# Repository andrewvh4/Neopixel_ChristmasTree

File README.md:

# Neopixel_ChristmasTree
A small, festive desk ornament

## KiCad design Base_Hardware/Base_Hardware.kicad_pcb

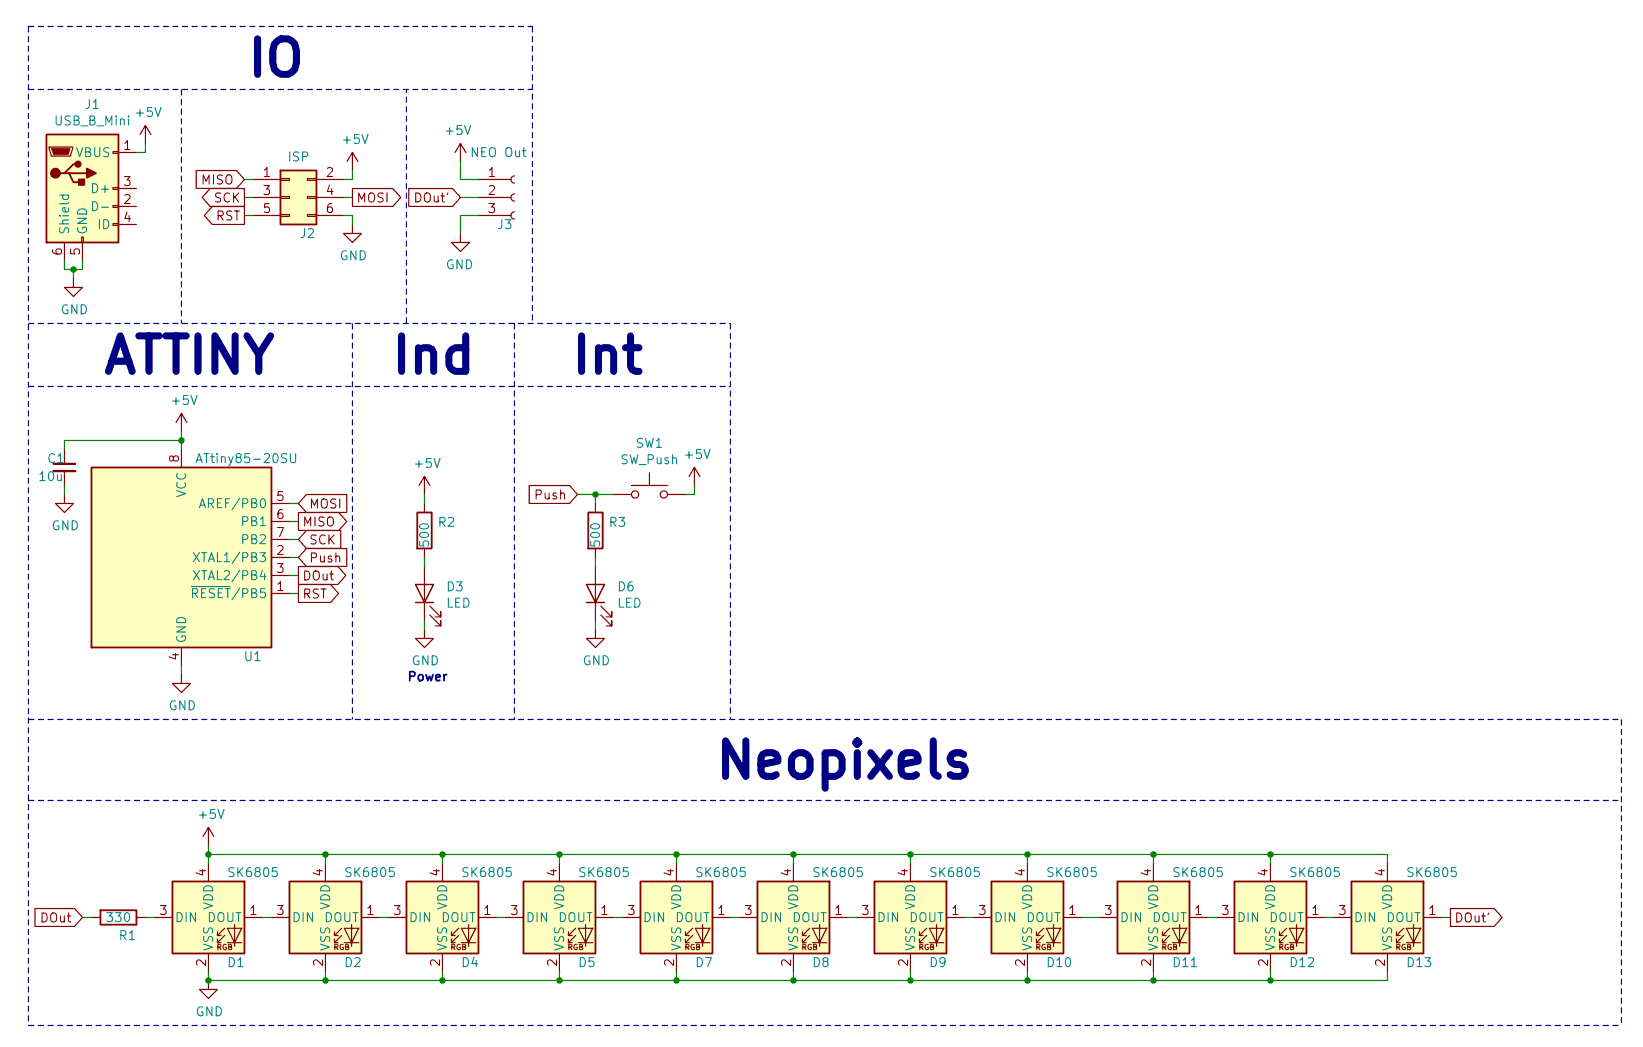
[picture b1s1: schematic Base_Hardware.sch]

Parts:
C1: 10u; C_0603_1608Metric_Pad1.05x0.95mm_HandSolder
D1, D2, D4, D5, D7, D8, D9, D10, D11, D12, D13: SK6805; SK6805-EC
D3, D6: LED; LED_0603_1608Metric_Pad1.05x0.95mm_HandSolder
J1: USB_B_Mini; MiniUSB_SMD
J2: ISP; IDC-Header_2x03_P2.54mm_Vertical
J3: NEO Out; PinSocket_1x03_P2.54mm_Vertical
R1: 330; R_0603_1608Metric_Pad1.05x0.95mm_HandSolder
R2, R3: 500; R_0603_1608Metric_Pad1.05x0.95mm_HandSolder
SW1: SW_Push; SW_SPST_PTS645
U1: ATtiny85-20SU; SOIJ-8_5.3x5.3mm_P1.27mm

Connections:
+5V: C1.1, D1.4 (VDD), D2.4 (VDD), D4.4 (VDD), D5.4 (VDD), D7.4 (VDD), D8.4 (VDD), D9.4 (VDD), D10.4 (VDD), D11.4 (VDD), D12.4 (VDD), D13.4 (VDD), J1.1 (VBUS), J2.2, J3.1, R2.1, SW1.2, U1.8 (VCC)
DOut: R1.2, U1.3 (XTAL2/PB4)
DOut': D13.1 (DOUT), J3.2
GND: C1.2, D1.2 (VSS), D2.2 (VSS), D3.1 (K), D4.2 (VSS), D5.2 (VSS), D6.1 (K), D7.2 (VSS), D8.2 (VSS), D9.2 (VSS), D10.2 (VSS), D11.2 (VSS), D12.2 (VSS), D13.2 (VSS), J1.5 (GND), J1.6 (Shield), J2.6, J3.3, U1.4 (GND)
MISO: J2.1, U1.6 (PB1)
MOSI: J2.4, U1.5 (AREF/PB0)
unnamed: D1.1 (DOUT), D2.3 (DIN)
unnamed: D1.3 (DIN), R1.1
unnamed: D2.1 (DOUT), D4.3 (DIN)
unnamed: D3.2 (A), R2.2
unnamed: D4.1 (DOUT), D5.3 (DIN)
unnamed: D5.1 (DOUT), D7.3 (DIN)
unnamed: D6.2 (A), R3.2
unnamed: D7.1 (DOUT), D8.3 (DIN)
unnamed: D8.1 (DOUT), D9.3 (DIN)
unnamed: D10.1 (DOUT), D11.3 (DIN)
unnamed: D9.1 (DOUT), D10.3 (DIN)
unnamed: D11.1 (DOUT), D12.3 (DIN)
unnamed: D12.1 (DOUT), D13.3 (DIN)
Push: R3.1, SW1.1, U1.2 (XTAL1/PB3)
RST: J2.5, U1.1 (~RESET~/PB5)
SCK: J2.3, U1.7 (PB2)

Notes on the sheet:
ATTINY
Neopixels
Power
Ind
Int

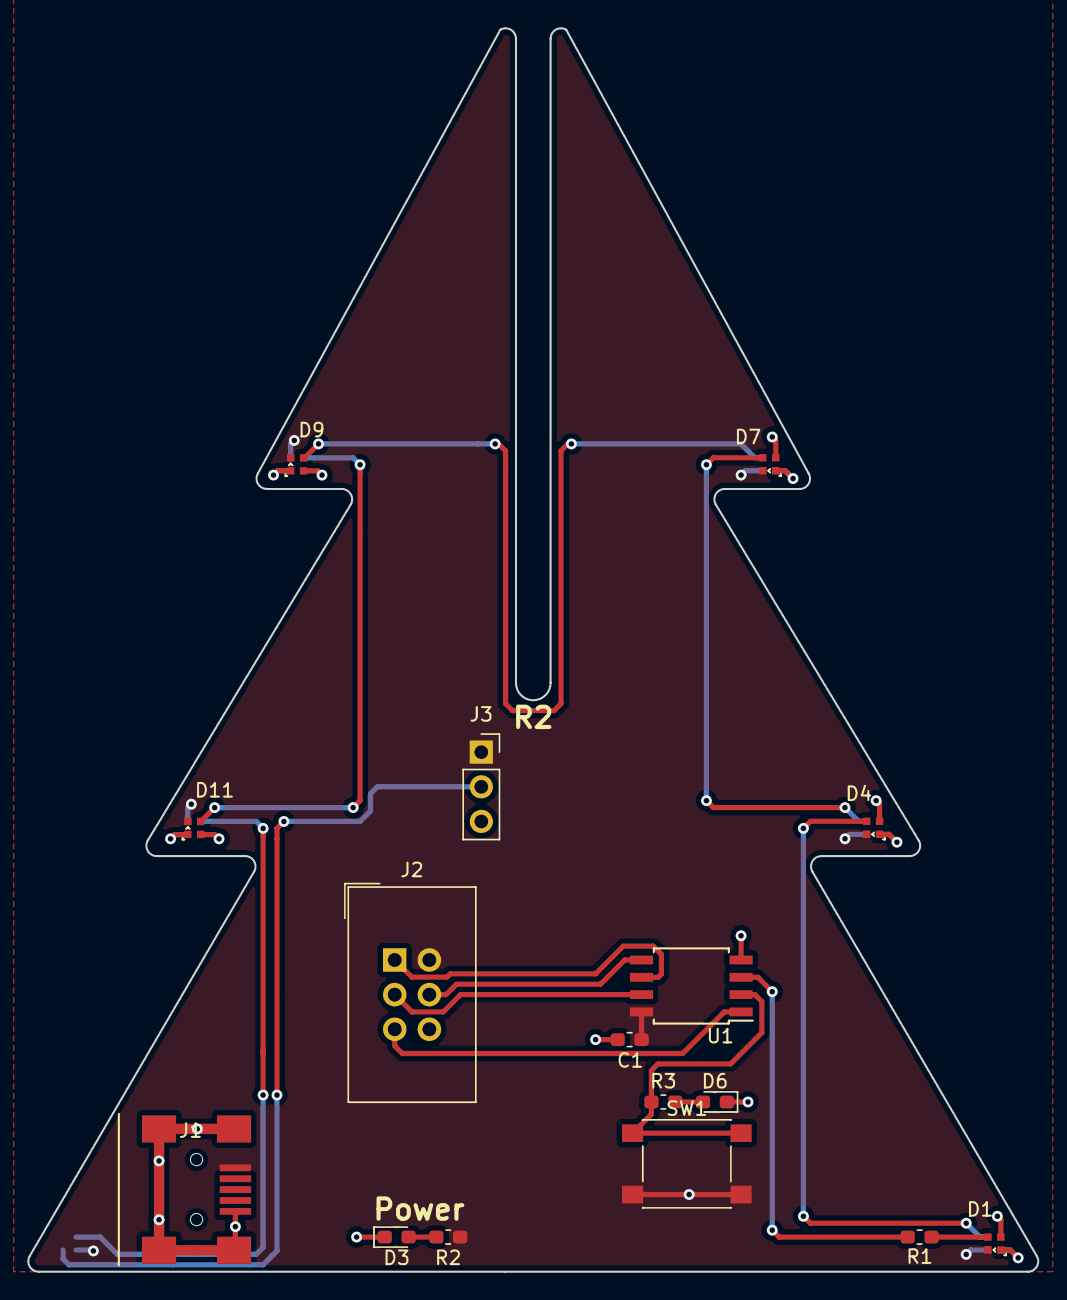
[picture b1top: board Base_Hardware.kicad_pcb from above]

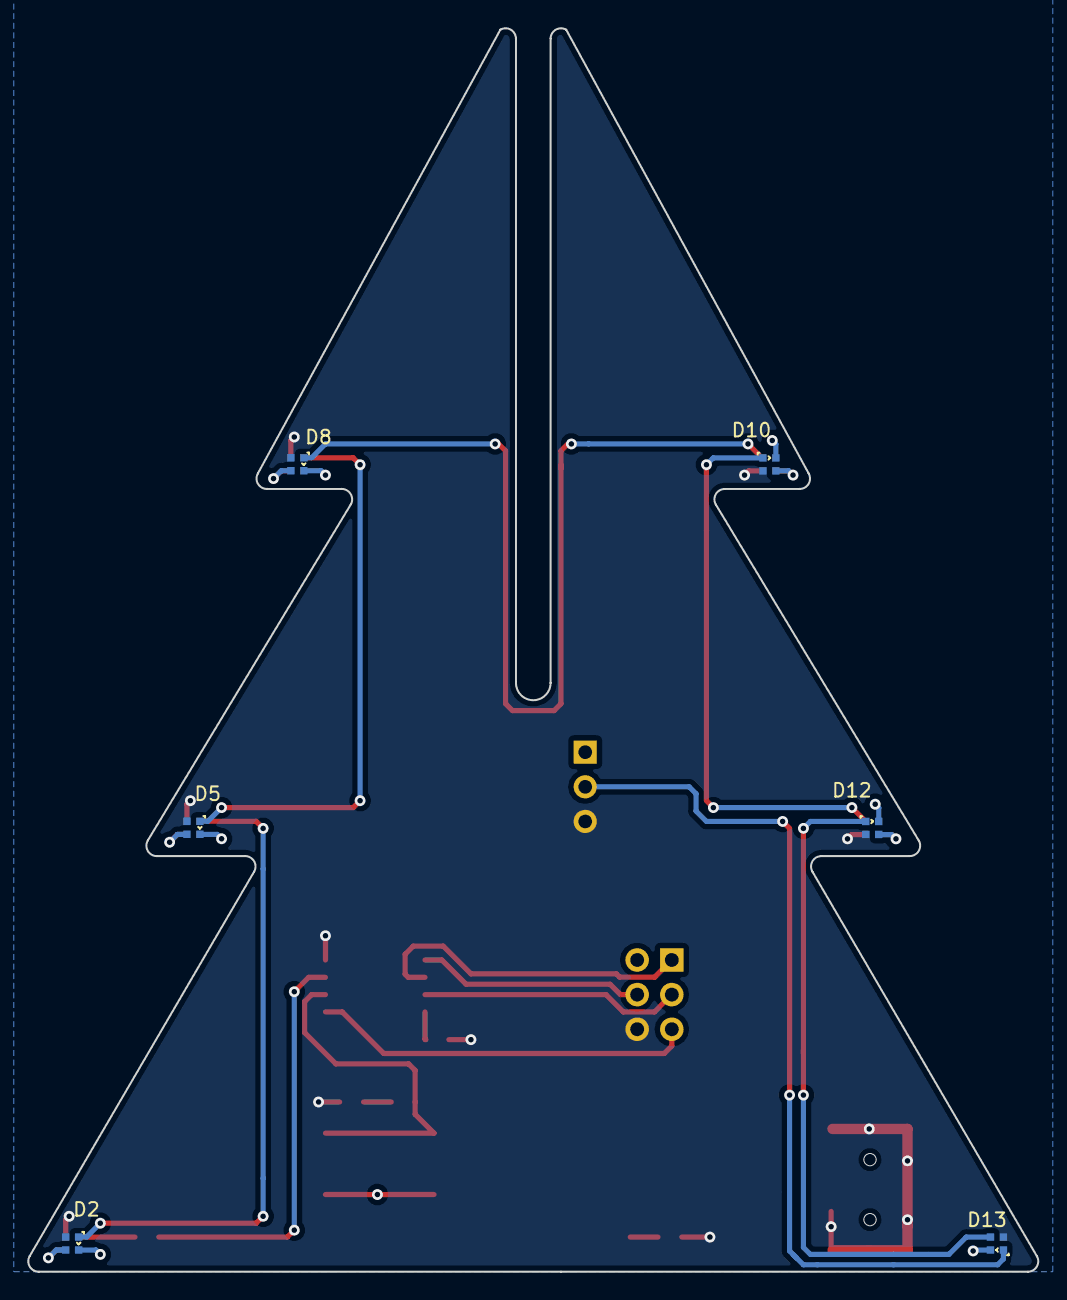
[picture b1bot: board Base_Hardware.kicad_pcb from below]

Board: 2 copper layers, 74.1 x 91.2 mm, 22 parts (6 on the bottom side), 22 nets.

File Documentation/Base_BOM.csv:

Id,Designator,Package,Designation,,Item Name,Part Number,,,Vendor,Quantity,Cost Per Item,,Cost,,Comments,URL
1,J1,MiniUSB_SMD,USB_B_Mini,,SMD Mini USB,151-1206-1-ND,,,Digikey,1,0.54,,0.54,,,https://www.digikey.com/product-detail/en/edac-inc/690-005-2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
2,C1,C_0603_1608Metric_Pad1.05x0.95mm_HandSolder,10u,,10uF 0603 Capacitor,490-10728-1-ND,,,Digikey,1,0.32,,0.32,,,https://www.digikey.com/product-detail/en/murata-electronics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
3,"D1,D2,D4,D5,D7,D8,D9,D10,D11,D12,D13,D14",LED_SK6805_PLCC4_2.4x2.7mm_P1.3mm,SK6805,,NEOPIXEL RGB LED 1515 SK6805-EC 15,1528-4492-ND,,,Digikey,12,0.395,,4.74,,,https://www.digikey.com/product-detail/en/4492/1528-4492-ND/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
4,"D3,D6",LED_0603_1608Metric_Pad1.05x0.95mm_HandSolder,LED,,LED 0603 Green,160-1443-1-ND,,,Digikey,2,0.23,,0.46,,,https://www.digikey.com/product-detail/en/lite-on-inc/LTST-C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
5,J2,IDC-Header_2x03_P2.54mm_Vertical,ISP,,IDC Header,3M15451-ND,,,Digikey,1,0.64,,0.64,,,https://www.digikey.com/product-detail/en/30306-6002HB/3M154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
6,J3,PinSocket_1x03_P2.54mm_Horizontal,NEO Out,,CONN HDR 3POS 0.1 TIN PCB R/A,S5439-ND,,,Digikey,1,0.5,,0.5,,,https://www.digikey.com/product-detail/en/sullins-connector-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
7,R1,R_0603_1608Metric_Pad1.05x0.95mm_HandSolder,330,,0603 Resistor 330,311-330HRCT-ND,,,Digikey,1,0.1,,0.1,,,https://www.digikey.com/product-detail/en/yageo/RC0603FR-073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
8,"R2,R3",R_0603_1608Metric_Pad1.05x0.95mm_HandSolder,500,,0603 Resistor 500,RHM510DCT-ND,,,Digikey,2,0.1,,0.2,,,https://www.digikey.com/product-detail/en/rohm-semiconductor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
9,SW1,SW_SPST_PTS645,SW_Push,,Pushbutton Switch,CKN9088CT-ND,,,Digikey,1,0.22,,0.22,,,https://www.digikey.com/products/en?keywords=CKN9088CT-ND
10,U1,SOIJ-8_5.3x5.3mm_P1.27mm,ATtiny85-20SU,,ATTINY85-20SUR,ATTINY85-20SURCT-ND,,,Digikey,1,1.19,,1.19,,,https://www.digikey.com/product-detail/en/microchip-technolo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

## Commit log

2020-06-02 Created Schematic
2020-06-02 Created Base Schematic
2020-06-05 assigned footprints
2020-06-06 created tree outlines
2020-06-06 modified connecting slit
2020-06-06 created todo
2020-06-06 Placed high-level components and traces
2020-06-11 Finished layout
